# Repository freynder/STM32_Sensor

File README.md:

# STM32 Sensor Node

A Small STM32F103C8T6 board with all functional pins exposed. Similar to the BluePill board except:

- no regulator. Will be powered by 2 AA batteries.
- no USB
- No LED
- No BOOT0/BOOT1 jumper pins. BOOT0 can be pulled high by a button, BOOT1 is pulled low permanently but exposed by a PIN.
- smaller crystals
- RFM69CW + RFM69(H)W + RFM69HCW footprints + u.FL connector
- VBAT can be disconnected from VCC by cutting the solder jumper on the back.

The size is 36.56mm x 20.32mm. 5 mils trace width and clearance. 20 mils edge clearance.

Tested succesfully V3 with jlcpcb order.
Test failed with V3.4 pcbs.io order due to imposed edge clearance. Should be corrected as of V4.3

## Top view

## Bottom view

## Version history
- V1: was never released because it was faulty and had less pins exposed.
- V2: had full pin availability but the layout was messy.
- V3: is V2 + u.FL connector + better layout and clearer markings.
- V3.3: corrected mislabeling + moved board edges to fit on breadboard (only sides).
- V3.4: moved labels so they are still visible when headers are soldered on. Optimized a few traces. Changed custom button footprint to RS282G05A3 buttons.
- as of V4 detailed history is tracked in git log.
- V5: Added RFM69(H)W footprints. Cleaned up git. Cleaned up tracks, fab layer, silk screen.

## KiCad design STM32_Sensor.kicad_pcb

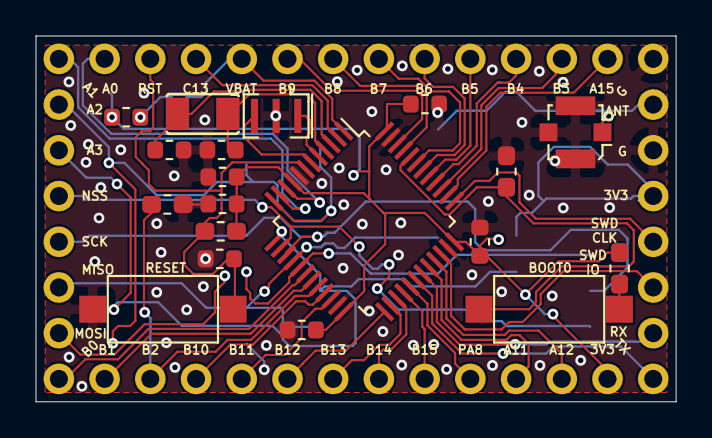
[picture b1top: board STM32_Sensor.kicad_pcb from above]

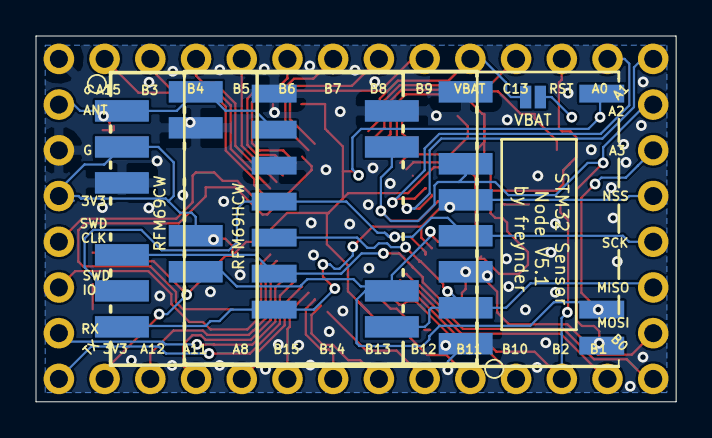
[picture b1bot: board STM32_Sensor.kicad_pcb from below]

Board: 2 copper layers, 35.6 x 20.3 mm, 27 parts (4 on the bottom side), 45 nets.

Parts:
C1: 1uF; C_0603_1608Metric
C2, C3, C4, C5: 0.1uF; C_0603_1608Metric
C6: 10uF; C_0603_1608Metric
C7: 100nF; C_0603_1608Metric
C8, C9: 10pF; C_0603_1608Metric
J1: Conn Side; PinSocket_1x08_P2.54mm_Vertical_Clear
J2: Conn Down; PinHeader_1x12_P2.54mm_Vertical_Clear
J3: Conn Up; PinHeader_1x12_P2.54mm_Vertical_Clear
J4: Conn Prog; PinSocket_1x08_P2.54mm_Vertical_Clear
J5: u.FL; U.FL_Molex_MCRF_73412-0110_Vertical
JP1: VBAT Jumper; SMT-JUMPER_2_NO_NO-SILK
R1, R2: 10K; R_0603_1608Metric_Pad1.05x0.95mm_HandSolder
R3, R4: 100K; R_0603_1608Metric_Pad1.05x0.95mm_HandSolder
SW1: SW_Reset; SW_SPST_CK_RS282G05A3
SW2: SW_BOOT; SW_SPST_CK_RS282G05A3
U1: STM32F103C8Tx; LQFP-48_7x7mm_P0.5mm
U2: RFM69CW; RFM69CW-XXXS2-MINPADS
U3: RFM69HW; HOPERF_RFM69HW-MINPADS
U4: RFM69HCW; RFM69HCW-XXXS2-MINPADS
Y1: 32768 Crystal; Seeedstudio-32kHz_Crystal-FC135
Y2: 8Mhz; Resonator_SMD_muRata_CSTxExxV-3Pin_3.0x1.1mm

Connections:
+3V3: C2.1, C3.1, C4.1, C5.1, C6.1, C7.1, J2.12, J4.4, R1.1, R2.1, U1.9, U1.24, U1.36, U1.48, U2.2, U3.8, U4.13
ANT: J4.2, J5.1, U2.1, U3.10, U4.9
BOOT0: R3.2, SW2.1, U1.44
GND: C1.2, C2.2, C3.2, C4.2, C5.2, C6.2, C8.2, C9.2, J4.1, J4.3, J5.2, R3.1, R4.1, SW1.1, U1.8, U1.23, U1.35, U1.47, U2.3, U2.14, U3.9, U3.11, U4.1, U4.8, U4.10, Y2.2
MISO: J1.6, U1.16, U2.8, U3.13, U4.2
MOSI: J1.7, U1.17, U2.5, U3.14, U4.3
NSS: J1.4, U1.14, U2.7, U3.15, U4.5
unnamed: C7.2, JP1.2
unnamed: R2.2, SW2.2
OSC1: U1.5, Y2.1
OSC2: U1.6, Y2.3
PA0: J3.12, U1.10
PA1: J1.1, U1.11
PA2: J1.2, U1.12, U2.13, U3.1, U4.6
PA3: J1.3, U1.13, U2.9, U3.2, U4.14
PA8: J2.9, U1.29
PA11: J2.10, U1.32
PA12: J2.11, U1.33
PA15: J3.1, U1.38
PB0: J1.8, U1.18
PB1: J2.1, U1.19
PB2: J2.2, R4.2, U1.20
PB3: J3.2, U1.39
PB4: J3.3, U1.40
PB5: J3.4, U1.41
PB6: J3.5, U1.42
PB7: J3.6, U1.43
PB8: J3.7, U1.45
PB9: J3.8, U1.46
PB10: J2.3, U1.21
PB11: J2.4, U1.22
PB12: J2.5, U1.25
PB13: J2.6, U1.26
PB14: J2.7, U1.27
PB15: J2.8, U1.28
PC13: J3.10, U1.2
RST: C1.1, J3.11, R1.2, SW1.2, U1.7
RTCOSC1: C8.1, U1.3, Y1.1
RTCOSC2: C9.1, U1.4, Y1.2
RX: J4.7, U1.31
SCK: J1.5, U1.15, U2.6, U3.12, U4.4
SWDCLK: J4.5, U1.37
SWDIO: J4.6, U1.34
TX: J4.8, U1.30
VBAT: J3.9, JP1.1, U1.1

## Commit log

2018-06-25 Initial
2018-06-29 Removed oscillator footprint overlap
2018-07-04 Minor changes to traces
2018-09-06 Added zones edge clearance
    Added 20 mils clearance between zones and edge to conform to pcbs.io
    manufacturing standards.
2018-09-07 Updated BOM with links and references
2018-09-08 Added support for RFM69(H)W
    Previously only RFM69CW and RFM69CHW were supported.
2018-09-10 Added support for RFM69HCW
    Previously only RFM69CW and RFM69(H)W were supported.
2018-09-10 Optimize fab and silk layer
2018-09-11 Cleaned up project
    Removed files that can be generated except for top and bottom
    images which are referenced in the README.md
2018-09-11 Made README nicer
2018-09-11 Created draft pinout diagram
2018-09-12 A few corrections to pinout diagram
2018-09-13 Some minor changes to pinout diagram
    still draft
2018-09-13 Made pinout nicer
2018-09-18 Routed the board with 6 mils traces/clearance
2018-09-24 Made VBAT jumper NO
    to comply with PCB manufacturer design rules.
